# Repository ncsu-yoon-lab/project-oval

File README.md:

# Project OVAL

**Project On-campus Vehicle Autonomous Launch (OVAL)** is a research and development project aimed at designing an autonomous vehicle capable of navigating NC State University's campus. The project provides a platform for students to test autonomous vehicle algorithms in a real-world environment. Additionally, it opens possibilities for campus applications such as package delivery, security patrols, plant monitoring, or other autonomous tasks.

The system architecture includes:

* **Onboard Computer (Jetson Orin)** – Runs the ROS2 packages in this repo for perception, control, telemetry, and navigation.
* **GUI Computer** – Provides a graphical interface for monitoring and control.
* **AWS EC2 Web Server** – Optional remote server for logging, telemetry, or additional processing.

💡 *Suggested addition:* A system diagram showing the connections between Jetson, sensors, GUI, and AWS could help new users visualize the setup.

---

## Repository Layout

This repo is a ROS2 `colcon` workspace `src/` checkout: every top-level `project_oval_*` folder is an independent `ament_python` package, discovered automatically when you run `colcon build` from the workspace root. There is no single monolithic package anymore — functionality is split by subsystem so each package can be built, tested, and depended on independently.

```
project_oval/                       # this repo (colcon workspace src/ checkout)
├── project_oval_control/           # driving & actuation
├── project_oval_perception/        # camera / ML perception
├── project_oval_telemetry/         # sensors & comms
├── project_oval_navigation/        # graph-based global navigation
├── project_oval_bringup/           # launch files, URDF, Webots world
├── PyVESC/                         # vendored VESC motor-controller protocol library
├── archive/                        # retired subsystems, excluded from the build (COLCON_IGNORE)
├── tools/                          # standalone scripts that aren't ROS packages
├── README.md
├── requirements.txt                # pip dependencies for all packages below (see Building)
├── ros2_command_guide.md           # colcon/ros2 command cheat sheet
└── version_control_guide.md        # day-to-day git command cheat sheet
```

Build everything with:

```bash
python3 -m pip install -r src/project_oval/requirements.txt   # once per machine — colcon doesn't do this for you
cd ~/ros2_ws   # workspace root, one level above src/
colcon build
source install/setup.bash
```

Build a single package while iterating:

```bash
colcon build --packages-select project_oval_control --symlink-install
```

`ros2 run`/`ros2 launch` won't find these packages until you `source install/setup.bash` in your current shell (a fresh terminal needs this every time, or add it to `.bashrc`) — see [`ros2_command_guide.md`](ros2_command_guide.md) for that and other frequently-used `colcon`/`ros2` commands.

### `project_oval_control` — driving & actuation

Turns steering/throttle/lane-following decisions into motor commands, and reads the Xbox controller for manual/teleop driving. Depends on the vendored `PyVESC/` library to talk to the VESC motor controllers over serial, plus `gps_msgs`/`nmea_msgs` for GPS-based pursuit.

| Run with | Purpose |
|---|---|
| `ros2 run project_oval_control driver` | Sends throttle/steering commands to the VESC motor controllers. |
| `ros2 run project_oval_control lane_follower` | PID lane-centering control from a segmented edge-distance signal. |
| `ros2 run project_oval_control xbox_controller` | Reads Xbox controller input (via `joy_node`) and republishes it as drive commands. |
| `ros2 launch project_oval_control manual_control.launch.py` | Brings up `joy_node` + `xbox_controller` + `driver` together for manual/teleop driving. |

Also included (not standalone nodes): `sim_driver_lib.py`/`sim_driver_node.py` (the `SimDriverNode` Webots plugin, wired up via `project_oval_bringup/urdf/my_robot.urdf` for simulation), `PIDController.py` (shared PID implementation), and `pursuitNode.py`/`test_lib.py` (older GPS-pursuit and manual test scripts, kept for reference — not registered as console scripts).

### `project_oval_perception` — camera & ML perception

Runs the computer-vision and ML models on camera input: sidewalk/lane segmentation and object detection.

| Run with | Purpose |
|---|---|
| `ros2 run project_oval_perception segmentation` | ONNX Runtime lane/sidewalk segmentation on the ZED camera feed. |
| `ros2 run project_oval_perception sidewalk_segmentation` | Transformer-based (Segformer) sidewalk segmentation using the bundled `sidewalk_segmentation_model/` weights. |
| `ros2 run project_oval_perception obstacle_detector` | LaserScan-based obstacle detection; publishes a brake/stop signal. |
| `ros2 run project_oval_perception yolo_od` | YOLO object detection on the camera feed. |
| `ros2 run project_oval_perception zed` | Publishes raw ZED camera images as a ROS2 topic. |

`lane_detector.py`/`simple_lane_detection.py` are shared detection library code (also imported by `project_oval_control`'s `lane_follower_node`). `docs/onnx_runtime_install_guide.md` has the ONNX Runtime GPU install steps for Jetson/ARM64.

> ⚠️ `segmentation_node.py`'s default model path and `test.py` still point at a contributor's personal machine (`/home/wolfwagen1/...`) and reference an ONNX model (`dino_segmentation_2.onnx`) that isn't checked into this repo. Point `model_path` at a real model (e.g. the bundled `sidewalk_segmentation_model/`) before relying on the `segmentation` executable.

### `project_oval_telemetry` — sensors & communications

Reads and republishes sensor/GPS data, bridges to external systems (a serial radio link, Google Cloud Pub/Sub), and displays status.

| Run with | Purpose |
|---|---|
| `ros2 run project_oval_telemetry imu` | Logs ZED IMU data to CSV. |
| `ros2 run project_oval_telemetry fake_rtk` | Publishes a synthetic RTK/GPS fix for testing without hardware. |
| `ros2 run project_oval_telemetry zed_heading` | Computes vehicle heading from magnetometer/IMU data. |
| `ros2 run project_oval_telemetry telemetry_ros2` | Serial bridge node — relays ROS2 messages to/from a radio-connected Raspberry Pi. |
| `ros2 run project_oval_telemetry pub_sub_google` | Publishes telemetry to a Google Cloud Pub/Sub topic. |
| `ros2 run project_oval_telemetry oval_message` | Publishes rotating status/sponsor messages to `/oval_message`. |
| `ros2 run project_oval_telemetry message_display` | Tkinter GUI that displays whatever `oval_message` is currently publishing. |
| `ros2 run project_oval_telemetry map_test` | Manual test script: parses NMEA GPS fixes and renders them on a Folium map. |

`export_imu_csv.py`/`export_rosbag_video.py` are offline analysis scripts for pulling IMU CSVs and depth video out of a recorded rosbag — run directly with `python3`, not as ROS nodes.

### `project_oval_navigation` — graph-based global navigation

A self-contained global-navigation stack: waypoint-graph planning over campus, EKF/RTK localization, pure-pursuit path following, and a browser dashboard for launching/monitoring the other nodes. See `project_oval_navigation/README.md` for the full waypoint/graph format and startup sequence.

| Run with | Purpose |
|---|---|
| `ros2 run project_oval_navigation global_planner_node` | Plans a route through the waypoint graph (`maps/graph_nodes.csv`, `maps/graph_edges.csv`). |
| `ros2 run project_oval_navigation global_set_reference` | Captures a lat/lon reference origin from the current RTK GPS + ZED pose. |
| `ros2 run project_oval_navigation pure_pursuit_node` | Pure-pursuit path following against the planned route. |
| `ros2 run project_oval_navigation oval_web_ui` | Local web dashboard for starting/stopping the nodes above (and the manual driver/Xbox controller from `project_oval_control`). |
| `ros2 launch project_oval_navigation sensors_bringup.launch.py` | Brings up the sensor stack needed for localization. |
| `ros2 launch project_oval_navigation localization.launch.py` | Runs the `robot_localization` EKF/navsat filters. |
| `ros2 launch project_oval_navigation control_nodes.launch.py` | Launches driver + xbox_controller (from `project_oval_control`) + pure pursuit together. |
| `ros2 launch project_oval_navigation rtk_control.launch.py` | Full localization + control stack for RTK-based driving. |

This package depends on `project_oval_control` at run time (for the `driver` and `xbox_controller` executables used by its launch files and web UI).

### `project_oval_bringup` — launch, URDF, simulation world

No nodes of its own — orchestrates the others.

* `launch/car_sim_launch.py` — launches the Webots simulator with `worlds/test_world.wbt` and attaches `project_oval_control`'s `SimDriverNode` via `urdf/my_robot.urdf`.
* `urdf/my_robot.urdf` — robot description used by the Webots driver plugin.
* `worlds/test_world.wbt` — the Webots simulation world.

```bash
ros2 launch project_oval_bringup car_sim_launch.py
```

### Other top-level folders

* **`PyVESC/`** — vendored copy of [LiamBindle/PyVESC](https://github.com/LiamBindle/PyVESC) (VESC motor controller serial protocol). Not a ROS package; `project_oval_control` imports it as a regular Python dependency.
* **`archive/`** — retired code kept for reference, marked with `archive/COLCON_IGNORE` so colcon skips it during a build. Currently holds `project-oval_legacy_sidewalk/`, the earlier LIDAR + sidewalk-following subsystem.
* **`tools/`** — scripts that aren't ROS packages and aren't built by colcon, e.g. `tools/gemini_chatbot/` (voice/chat control demo scripts, run directly with `python3`).

---

## Startup Sequence for Onboard Computer (Jetson Orin)

The Jetson Orin runs several ROS2 nodes to interface with the vehicle hardware. The primary ones are:

| Node | Package | Purpose |
|---|---|---|
| `joy_node` | `joy` (external) | Reads XBox controller inputs |
| `swiftnav_ros2_driver` | `swiftnav_ros2_driver` (external) | Interfaces with the Piksi Multi GNSS |
| `zed_camera` | `zed_wrapper` (external) | Streams stereo camera data |
| `xbox_controller` | `project_oval_control` | Turns joystick input into drive commands |
| `driver` | `project_oval_control` | Sends commands to the motors |

---

### **Joy Node**

Outputs joystick inputs from the XBox controller.

```bash
ros2 run joy joy_node --ros-args -p autorepeat_rate:=20.0
```

---

### **Manual Driving (Joy + Xbox Controller + Driver)**

Brings up `joy_node`, `xbox_controller`, and `driver` together in one command — the quickest way to get manual/teleop driving running.

```bash
ros2 launch project_oval_control manual_control.launch.py
```

---

### **Lidar Node**

Outputs Lidar Pointcloud.

```bash
ros2 launch velodyne velodyne-all-nodes-VLP16-launch.py
```

To viz:

```bash
rviz2 ## change to velodyne frame
```

---

### **Message Display**

Show the Team and other messages.

```bash
ros2 run project_oval_telemetry message_display   # shows the GUI
ros2 run project_oval_telemetry oval_message       # publishes messages for the GUI to display
```

---

### **Gemini Voice Controller**

Control the robot using voice commands. This is a standalone script (`tools/`), not a ROS package.

```bash
python3 tools/gemini_chatbot/wolfwagen_live_demo.py ## To show GUI and listen
```

---

### **Radio Raspberry Pi Control**

Bridges ROS2 messages to a radio-connected Raspberry Pi over serial.

```bash
ros2 run project_oval_telemetry telemetry_ros2 ## To connect to Radio
```

---

### **ZED Camera Node**

Outputs ZED camera topics. Documentation: [Stereolabs ZED ROS2 Node](https://www.stereolabs.com/docs/ros/zed-node).

```bash
ros2 launch zed_wrapper zed_camera.launch.py camera_model:=zed2i
```

#### ZED2i Setup

1. **Check CUDA installation**

```bash
nvidia-smi
```

2. **Install ZED SDK**
   Follow the [official ZED SDK installation instructions](https://www.stereolabs.com/developers/release/latest/) for NVIDIA Jetson. This may take \~30 minutes.

3. **Set up the environment**
   Follow the [ROS2 environment setup instructions](https://www.stereolabs.com/docs/ros2).

💡 *Suggested addition:* Include instructions for testing the ZED camera stream after setup.

---

### **RTK Piksi Multi Setup**

Setup instructions for the SwiftNav Piksi Multi ROS2 package.

#### Step 1 – Installation

Follow the [SwiftNav ROS2 package instructions](https://github.com/swift-nav/swiftnav-ros2).

#### Step 2 – TCP Connection Setup

If TCP connection issues occur, set up the Jetson Ethernet interface manually:

```bash
sudo ip addr add 192.168.0.100/24 dev eno1
ping 192.168.0.222
```

#### Step 3 – Optional USB Setup

USB may be preferable to avoid Ethernet setup. Some RS232-to-USB adapters may not work on the Jetson due to missing drivers.

Check for the PL2303 driver:

```bash
zcat /proc/config.gz | grep -i 'pl2303'
```

If it returns `#CONFIG_USB_SERIAL_PL2303 is not set`, use an FTDI or CH340/CH341 adapter.

#### Step 4 – Run the Node

```bash
ros2 launch swiftnav_ros2_driver start.py
```

💡 *Suggested addition:* Add a small troubleshooting section for common GNSS issues (e.g., no fix, bad TCP connection).

---

### **PyVESC Library Setup**

PyVESC is already vendored in this repo at `PyVESC/` (unmodified copy of [LiamBindle/PyVESC](https://github.com/LiamBindle/PyVESC) v1.0.5) — you don't need to clone it separately.

#### Step 1 – Install it in editable mode

```bash
cd ~/ros2_ws/src/project_oval
python3 -m pip install -e PyVESC/
python3 -m pip install pyserial
```

#### Step 2 – Build and test the driver node

```bash
cd ~/ros2_ws
colcon build --packages-select project_oval_control --symlink-install
source install/setup.bash
ros2 run project_oval_control driver
```

💡 *Suggested addition:* Include instructions for ROS2 integration with PyVESC and how to verify motor actuation.

---

# GitHub Contribution Guidelines

This repository follows a lightweight but strict Git workflow to keep development organized, reviewable, and stable—especially important for autonomous vehicle development where software, simulation, and hardware intersect.

Please read and follow these rules before contributing. For everyday git commands (branching, pulling, pushing), see [`version_control_guide.md`](version_control_guide.md).

---

## 1. Branch Lifespan

**Branches should be short-lived.**

- If you create a new branch, it should be **merged or closed within 7 days**.
- If work is ongoing past a week:
  - Open a pull request with incremental progress, or
  - Clearly note why the branch is staying open.

This helps prevent abandoned branches and keeps development moving.

---

## 2. Pull Requests for All Changes

**All changes must go through pull requests.**

- Any successful or functional change—no matter how small—should be submitted as a pull request.
- Draft pull requests are encouraged for incomplete or in-progress work.
- This applies even if you are the only one working on the branch.

Pull requests are used to track changes to `main`, discuss design decisions, and preserve project history.

---

## 3. One Purpose per Branch

**Each branch should have a single, clear purpose.**

- Avoid mixing unrelated changes in the same branch.
- Examples of unrelated changes:
  - Sensor drivers + visualization tweaks
  - Control logic + documentation cleanup

Keeping branches focused makes reviews, testing, and debugging significantly easier.

---

## 5. Pull Request Descriptions

**Every pull request must include:**

- **What changed**
- **Why it changed**
- **How it was tested**
  - Simulation
  - Hardware
  - Log playback
  - Or explicitly state if it was not tested

Clear PR descriptions save time and reduce misunderstandings.

---

## 6. No Direct Pushes to `main`

**Direct pushes to `main` are not allowed.**

- All changes must be merged through pull requests.
- This rule applies to everyone, regardless of role.

This ensures visibility, review, and traceability of all changes.

---

## 7. Keep `main` Runnable

**The `main` branch must always build and run.**

- Do not merge changes that break:
  - Builds
  - Simulation
  - Deployment pipelines
- If a change introduces a breaking issue, it must be fixed before merging.

`main` should always represent a stable, usable state of the project.

---

## 8. Commit Hygiene

**Commits should be clear and intentional.**

- Use descriptive commit messages.
- Avoid vague messages like:
  - `wip`
  - `fix`
  - `stuff`
- Each commit should represent a coherent, logical change.

Good commit history makes debugging, reverting, and collaboration far easier.

---

## Final Notes

These rules exist to:
- Prevent branch sprawl
- Keep `main` stable
- Make collaboration and review painless
- Save time during testing, deployment, and field work

If something doesn't fit neatly into these rules, communicate early via a pull request or discussion.

### **Additional Recommendations for README**

1. **System Requirements:** List Jetson OS version, ROS2 version, Python version, and minimum hardware requirements.
2. **Startup Script:** Consider creating a single script to launch all nodes in the correct order.
3. **Troubleshooting Section:** Include common error messages for ROS2, ZED, Piksi Multi, and PyVESC.
4. **Data Logging:** Provide instructions for recording sensor or GNSS data for research purposes.
5. **References:** Include links to relevant ROS2, ZED, Piksi, and PyVESC documentation for quick reference.

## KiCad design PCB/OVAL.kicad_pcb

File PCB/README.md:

# Project OVAL PCB

## Overview
The electronics system is designed and developed with the use of [KiCAD](https://www.kicad.org/) to incorporate the entire electrical system into a printed circuit board (PCB). The PCB will be manufactured by [JLCPCB](https://jlcpcb.com/). Developing a custom PCB will provide consistent connections and further adjustments as new revisions are made on the PCB.

## KiCAD Version Control
You can access the project by importing the .proj file in this directory. Do not change anything unless collaborating with other members.

## Next Steps
* Schematic needs to be checked
* Test ATTiny85 with I2C and PPM generation
* Figure out wiring for back LEDs
* Power switch for ESC
* Make the ESC directly attach to the PCB
* Remove the electromagnets
* Include a voltage sensor

## Components
Below are the descriptions of all the components considered and incorporated into the PCB

### Power
The power for the whole system is sourced from two [4s LiPo batteries](https://www.amazon.com/dp/B07Y1PYHKC?ref_=ppx_hzsearch_conn_dt_b_fed_asin_title_2). Turning the power on and off is directly controlled by a [DPDT switch](https://www.amazon.com/Twidec-Rocker-Toggle-Position-Waterproof/dp/B07LBMMN2Y/ref=sr_1_3?dib=eyJ2IjoiMSJ9.H1GVn0sV9nroy_uFaZHPdd5zl96OmoEBumcDbs2H2JQsCQWccp83BUf9UMrdTw5yn2Gh-R7XMM7Rhy0J8cPQUunQYQQI-I8DpZY4GHWhhZfa_H08-9tdhQhasKEfKwsORwEHOc4Qq9w2f_awsDMn9SciTHHxJvrF6eQ4TpXpnHJhAdd_uB5lI0awRb96oNr2xs-qYPh7MeJv7FwMkOd6xVZB6cMgUIFhQ-2nyexbUGw.bw0kXIxRu6rnZ9yNmepIGsJ9vjd-tjA7nIPwPtc036g&dib_tag=se&keywords=double%2Bpole%2Bdouble%2Bthrow%2Bswitch&qid=1748457096&sr=8-3&th=1). The power then goes through a [buck converter](https://www.amazon.com/WWZMDiB-Converter-Adjustable-Regulator-Protection/dp/B0B825HRB9/ref=sr_1_3?crid=X0NHTXOBZQBN&dib=eyJ2IjoiMSJ9.OVZkkMvTynFktJV0_FpqOz9G-79GCf5LbvPXwQiyANJTXUIdp-s9YyWXiubRIaMcQTqaOvUStJel0N4QgSzktCbwemDFsNzsKFPukLzzg9BAYQ7lPAzqoRV9t5gccvsWanqf6VVNeu8hhikXhyIUT0Np_qtc4yjpI7uwknCNYr7hk-_KrTu2k3UAdGd2GWSzxy316hXX1D9F4PrttX0l6_WxYWf5SUisVcA2T02Gyiw._XYZ6-QOanhcWZ5D29KLau23OnrpKjCr3EAjNbOWu8I&dib_tag=se&keywords=buck+converter+high+current&qid=1748453761&sprefix=buck+converter+high+current%2Caps%2C113&sr=8-3) to convert the output of the batteries to 12VDC and a max of 20A. This power will go to several features: cooling system, NVIDIA Jetson Orin AGX, monitoring LED, and the external 12VDC plug on the panel. A DC to DC converter is used to then convert the 12VDC to 5VDC to power the front LED and the touch screen.

### Charging
The batteries are expected to remain inside the electronics box at all times and are only able to be charged and discharged when the system is turned off via the [DPDT switch](https://www.amazon.com/Twidec-Rocker-Toggle-Position-Waterproof/dp/B07LBMMN2Y/ref=sr_1_3?dib=eyJ2IjoiMSJ9.H1GVn0sV9nroy_uFaZHPdd5zl96OmoEBumcDbs2H2JQsCQWccp83BUf9UMrdTw5yn2Gh-R7XMM7Rhy0J8cPQUunQYQQI-I8DpZY4GHWhhZfa_H08-9tdhQhasKEfKwsORwEHOc4Qq9w2f_awsDMn9SciTHHxJvrF6eQ4TpXpnHJhAdd_uB5lI0awRb96oNr2xs-qYPh7MeJv7FwMkOd6xVZB6cMgUIFhQ-2nyexbUGw.bw0kXIxRu6rnZ9yNmepIGsJ9vjd-tjA7nIPwPtc036g&dib_tag=se&keywords=double%2Bpole%2Bdouble%2Bthrow%2Bswitch&qid=1748457096&sr=8-3&th=1). The batteries will be ran in parallel to extend the battery life of the 2 4s LiPo batteries to last an hour of driving at half speed.

### Motor Control
Each motor will be driven via an [ATTiny85](https://www.microchip.com/en-us/product/attiny85). The two ATTiny85s are an AVR that will be on an I2C bus with the NVIDIA Jetson Orin AGX as the parent to receive a command on the throttle. The ATTiny85 will separately output a PPM signal to the ESCs to control the throttle of the motors. Currently untested.

### Access Panel
Inside the tailgate of the system there will be an access panel to all the features inside the electronics box to avoid having to remove the electronics box at any time. The access panel will include charging ports for battery 1 and 2, USB A and USB C ports to the Orin, pins to the Orin, OLED screen displaying battery life, LED displaying power on/off, display port to the Orin, and the toggle switch for powering the system, and a DC jack to access 12VDC if needed for testing.

## [Current parts list](https://docs.google.com/spreadsheets/d/1QfchhVsQ0_ZyLnvvQ3l3CDZhC2zzI9vGqhxGo_DR1Cs/edit?usp=sharing)
Feel free to add new parts if needed.

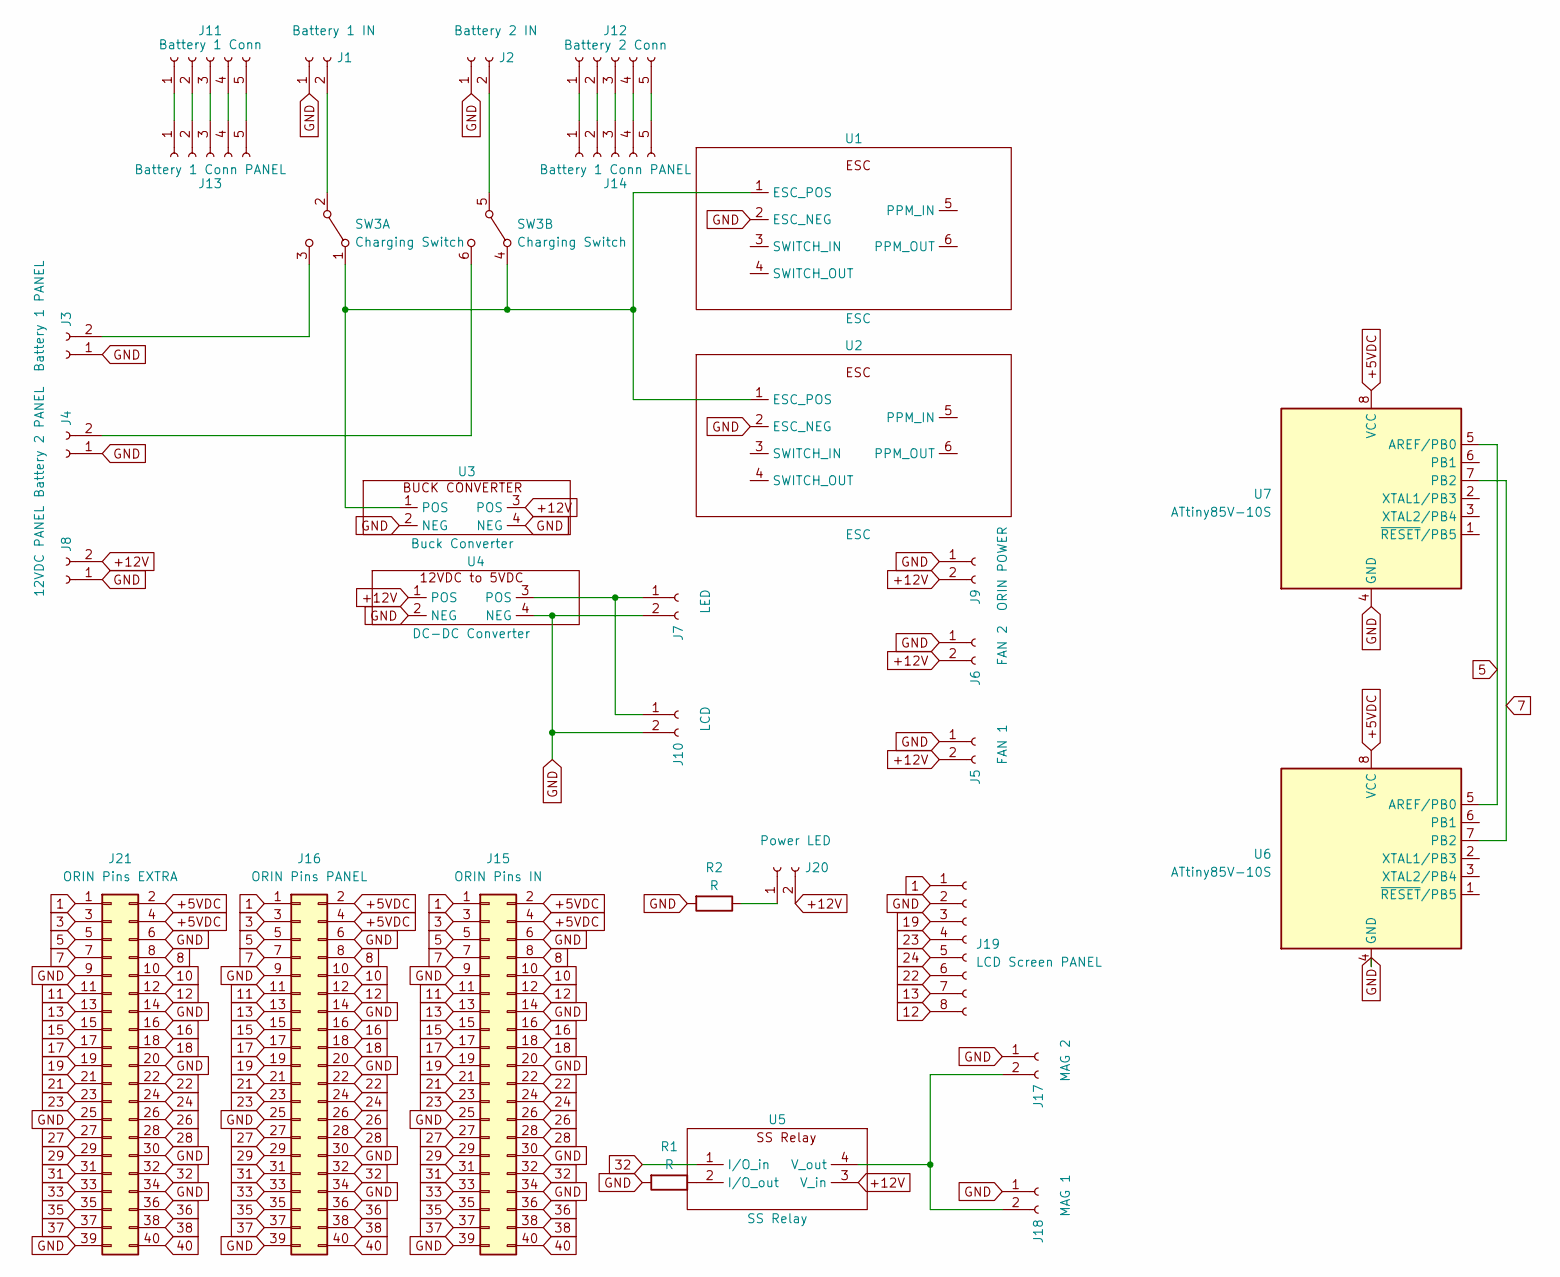
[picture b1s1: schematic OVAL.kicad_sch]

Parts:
J1: Battery 1 IN; BATTERY
J2: Battery 2 IN; BATTERY
J3: Battery 1 PANEL; BATTERY
J4: Battery 2 PANEL; BATTERY
J5: FAN 1; PinSocket_1x02_P2.54mm_Vertical
J6: FAN 2; PinSocket_1x02_P2.54mm_Vertical
J7: LED; PinSocket_1x02_P2.54mm_Vertical
J8: 12VDC PANEL; BATTERY
J9: ORIN POWER; PinSocket_1x02_P2.54mm_Vertical
J10: LCD; PinSocket_1x02_P2.54mm_Vertical
J11: Battery 1 Conn; PinSocket_1x05_P2.54mm_Vertical
J12: Battery 2 Conn; PinSocket_1x05_P2.54mm_Vertical
J13, J14: Battery 1 Conn PANEL; PinSocket_1x05_P2.54mm_Vertical
J15: ORIN Pins IN; PinSocket_2x20_P2.54mm_Vertical
J16: ORIN Pins PANEL; PinSocket_2x20_P2.54mm_Vertical
J17: MAG 2; PinSocket_1x02_P2.54mm_Vertical
J18: MAG 1; PinSocket_1x02_P2.54mm_Vertical
J19: LCD Screen PANEL; PinSocket_1x08_P2.54mm_Vertical
J20: Power LED; PinSocket_1x02_P2.54mm_Vertical
J21: ORIN Pins EXTRA; PinSocket_2x20_P2.54mm_Vertical
R1, R2: R; R_Axial_DIN0207_L6.3mm_D2.5mm_P10.16mm_Horizontal
SW3: Charging Switch; PinSocket_1x06_P2.54mm_Vertical
U1, U2: ESC
U3: Buck Converter; Buck_Converter
U4: DC-DC Converter; DC-DC_Converter
U5: SS Relay; SS_Relay
U6, U7: ATtiny85V-10S; SOIC-8W_5.3x5.3mm_P1.27mm

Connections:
1: J15.1, J16.1, J19.1, J21.1
3: J15.3, J16.3, J21.3
5: J15.5, J16.5, J21.5, U6.5 (AREF/PB0), U7.5 (AREF/PB0)
7: J15.7, J16.7, J21.7, U6.7 (PB2), U7.7 (PB2)
8: J15.8, J16.8, J21.8
10: J15.10, J16.10, J21.10
11: J15.11, J16.11, J21.11
12: J15.12, J16.12, J19.8, J21.12
13: J15.13, J16.13, J19.7, J21.13
15: J15.15, J16.15, J21.15
16: J15.16, J16.16, J21.16
17: J15.17, J16.17, J21.17
18: J15.18, J16.18, J21.18
19: J15.19, J16.19, J19.3, J21.19
21: J15.21, J16.21, J21.21
22: J15.22, J16.22, J19.6, J21.22
23: J15.23, J16.23, J19.4, J21.23
24: J15.24, J16.24, J19.5, J21.24
26: J15.26, J16.26, J21.26
27: J15.27, J16.27, J21.27
28: J15.28, J16.28, J21.28
29: J15.29, J16.29, J21.29
31: J15.31, J16.31, J21.31
32: J15.32, J16.32, J21.32, U5.1 (I/O_in)
33: J15.33, J16.33, J21.33
35: J15.35, J16.35, J21.35
36: J15.36, J16.36, J21.36
37: J15.37, J16.37, J21.37
38: J15.38, J16.38, J21.38
40: J15.40, J16.40, J21.40
+5VDC: J15.2, J15.4, J16.2, J16.4, J21.2, J21.4, U6.8 (VCC), U7.8 (VCC)
+12V: J5.2, J6.2, J8.2, J9.2, J20.2, U3.3 (POS), U4.1 (POS), U5.3 (V_in)
GND: J1.1, J2.1, J3.1, J4.1, J5.1, J6.1, J7.2, J8.1, J9.1, J10.2, J15.6, J15.9, J15.14, J15.20, J15.25, J15.30, J15.34, J15.39, J16.6, J16.9, J16.14, J16.20, J16.25, J16.30, J16.34, J16.39, J17.1, J18.1, J19.2, J21.6, J21.9, J21.14, J21.20, J21.25, J21.30, J21.34, J21.39, R1.2, R2.2, U1.2 (ESC_NEG), U2.2 (ESC_NEG), U3.2 (NEG), U3.4 (NEG), U4.2 (NEG), U4.4 (NEG), U6.4 (GND), U7.4 (GND)
unnamed: J1.2, SW3.2 (B)
unnamed: J2.2, SW3.5 (B)
unnamed: J3.2, SW3.3 (C)
unnamed: J4.2, SW3.6 (C)
unnamed: J7.1, J10.1, U4.3 (POS)
unnamed: J11.1, J13.1
unnamed: J11.2, J13.2
unnamed: J11.3, J13.3
unnamed: J11.4, J13.4
unnamed: J11.5, J13.5
unnamed: J12.1, J14.1
unnamed: J12.2, J14.2
unnamed: J12.3, J14.3
unnamed: J12.4, J14.4
unnamed: J12.5, J14.5
unnamed: J17.2, J18.2, U5.4 (V_out)
unnamed: J20.1, R2.1
unnamed: SW3.1 (A), SW3.4 (A), U1.1 (ESC_POS), U2.1 (ESC_POS), U3.1 (POS)
unnamed: R1.1, U5.2 (I/O_out)

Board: 2 copper layers, 31 parts (0 on the bottom side), 52 nets, no tracks yet.

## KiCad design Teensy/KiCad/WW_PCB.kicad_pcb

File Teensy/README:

Teensy loader commands for ORIN:

sudo cp 00-teensy.rules /etc/udev/rules.d/
tar -xvzf teensy_linux64.tar.gz

To use the teensy loader:
./teensy &

Other resources:
https://www.pjrc.com/teensy/td_download.html

https://www.pjrc.com/teensy/loader_linux.html

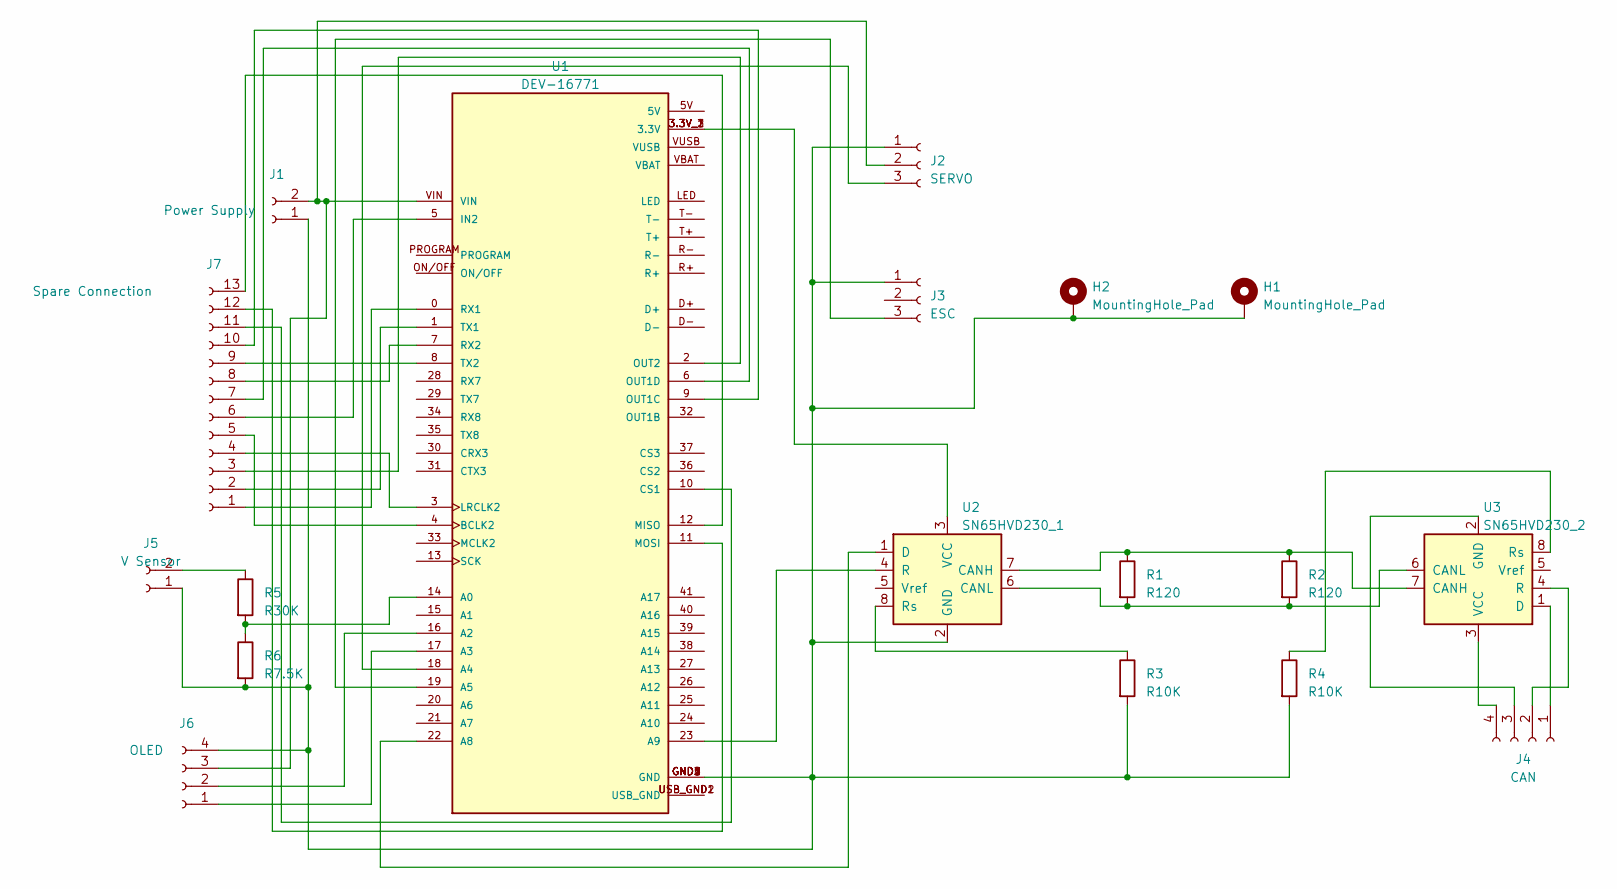
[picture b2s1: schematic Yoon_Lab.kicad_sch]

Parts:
H1, H2: MountingHole_Pad; MountingHole_3.2mm_M3_ISO14580_Pad
J1: Power Supply; PinSocket_1x02_P2.54mm_Horizontal
J2: SERVO; PinSocket_1x03_P2.54mm_Horizontal
J3: ESC; PinSocket_1x03_P2.54mm_Horizontal
J4: CAN; PinSocket_1x04_P2.54mm_Horizontal
J5: V Sensor; PinSocket_1x02_P2.54mm_Vertical
J6: OLED; PinSocket_1x04_P2.54mm_Vertical
J7: Spare Connection; PinSocket_1x13_P2.54mm_Vertical
R1, R2: R120; R_Axial_DIN0309_L9.0mm_D3.2mm_P12.70mm_Horizontal
R3, R4: R10K; R_Axial_DIN0309_L9.0mm_D3.2mm_P12.70mm_Horizontal
R5: R30K; R_Axial_DIN0309_L9.0mm_D3.2mm_P12.70mm_Horizontal
R6: R7.5K; R_Axial_DIN0309_L9.0mm_D3.2mm_P12.70mm_Horizontal
U1: DEV-16771; MODULE_DEV-16771; PARTREV 4.1
U2: SN65HVD230_1; SOIC-8_3.9x4.9mm_P1.27mm
U3: SN65HVD230_2; SOIC-8_3.9x4.9mm_P1.27mm

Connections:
unnamed: H1.1, H2.1, J1.1, J2.1, J3.1, J5.1, J6.4, R3.2, R4.2, R6.2, U1.GND1 (GND), U1.GND2 (GND), U1.GND3 (GND), U1.GND4 (GND), U1.GND5 (GND), U2.2 (GND)
unnamed: J1.2, J2.2, J6.3, U1.VIN
unnamed: J2.3, U1.18 (A4)
unnamed: J3.3, U1.19 (A5)
unnamed: J4.1, U3.1 (D)
unnamed: J4.2, U3.4 (R)
unnamed: J4.3, U3.2 (GND)
unnamed: J4.4, U3.3 (VCC)
unnamed: J5.2, R5.1
unnamed: J6.1, U1.17 (A3)
unnamed: J6.2, U1.16 (A2)
unnamed: J7.1, U1.0 (RX1)
unnamed: J7.2, U1.1 (TX1)
unnamed: J7.3, U1.2 (OUT2)
unnamed: J7.4, U1.3 (LRCLK2)
unnamed: J7.5, U1.4 (BCLK2)
unnamed: J7.6, U1.5 (IN2)
unnamed: J7.7, U1.6 (OUT1D)
unnamed: J7.8, U1.7 (RX2)
unnamed: J7.9, U1.8 (TX2)
unnamed: J7.10, U1.9 (OUT1C)
unnamed: J7.11, U1.10 (CS1)
unnamed: J7.12, U1.11 (MOSI)
unnamed: J7.13, U1.12 (MISO)
unnamed: R5.2, R6.1, U1.14 (A0)
unnamed: U1.22 (A8), U2.1 (D)
unnamed: U1.23 (A9), U2.4 (R)
unnamed: U1.USB_GND1 (USB_GND), U1.USB_GND2 (USB_GND)
unnamed: R1.1, R2.1, U2.7 (CANH), U3.7 (CANH)
unnamed: R1.2, R2.2, U2.6 (CANL), U3.6 (CANL)
unnamed: R3.1, U2.8 (Rs)
unnamed: U1.3.3V_1 (3.3V), U1.3.3V_2 (3.3V), U1.3.3V_3 (3.3V), U2.3 (VCC)
unnamed: R4.1, U3.8 (Rs)

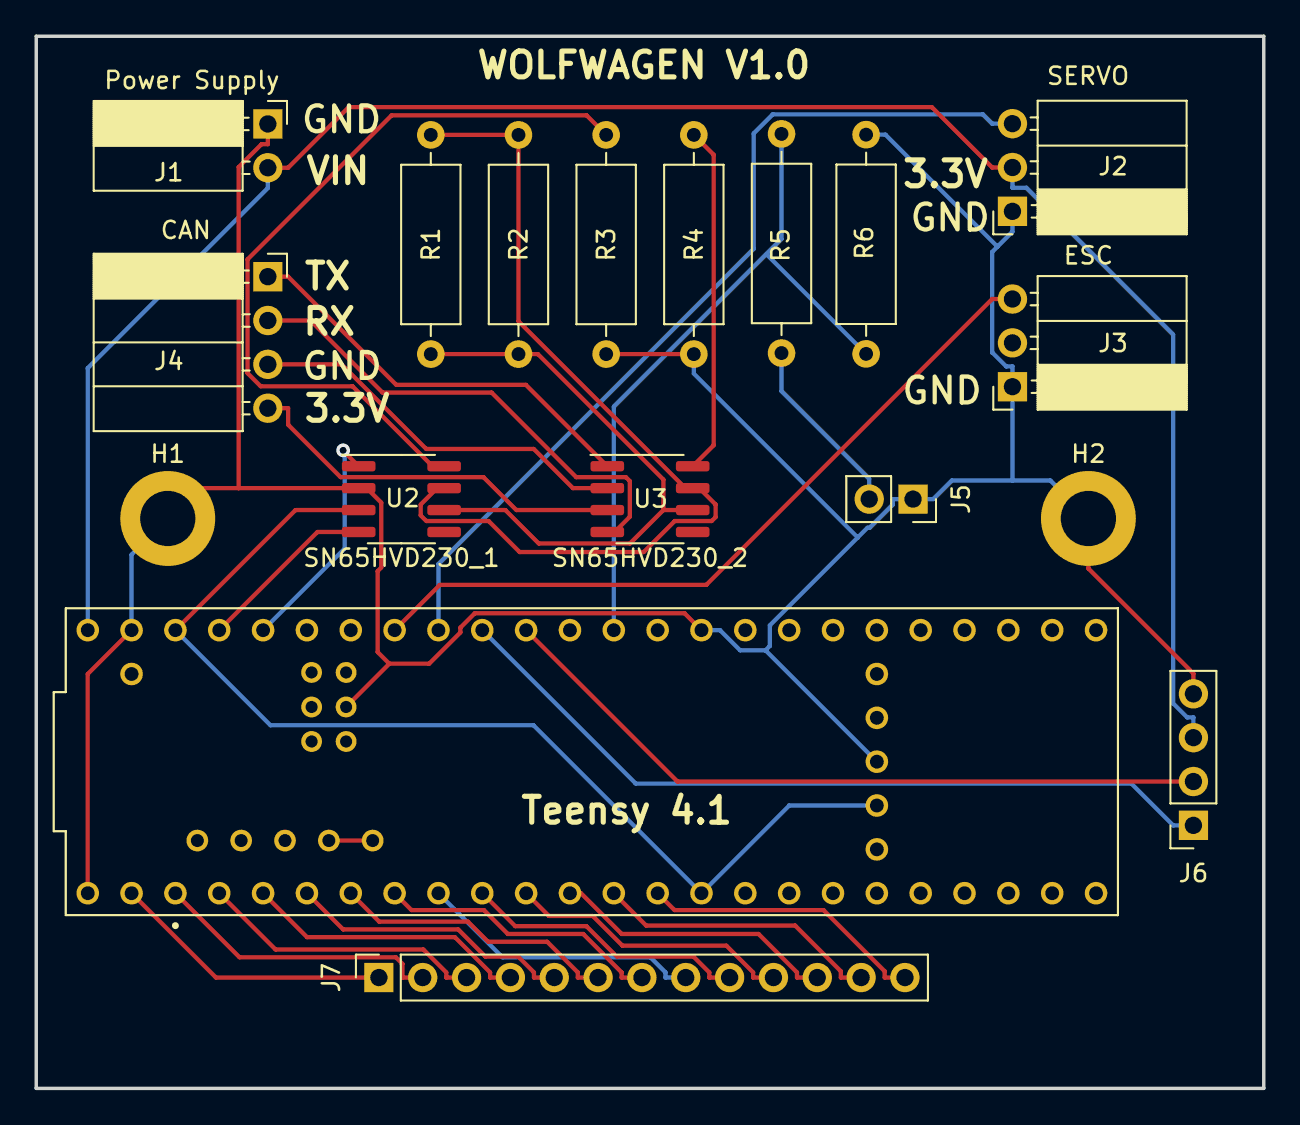
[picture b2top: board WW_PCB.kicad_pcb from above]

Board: 2 copper layers, 71.1 x 61.0 mm, 18 parts (0 on the bottom side), 33 nets.

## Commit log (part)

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2024-06-10 Rename node_gps.py to project-oval/node_gps.py
2024-06-10 Rename GUI/WW_Logo.png to GUI/Images/WW_Logo.png
2024-06-10 Rename GUI/blue_marker.png to GUI/Images/blue_marker.png
2024-06-10 Rename GUI/red_marker.png to GUI/Images/red_marker.png
2024-06-10 Rename WolfwagenBW.png to Wolfwagen-Horizontal-BW.png
2024-06-10 Rename Images/output-onlinepngtools.png to Wolfwagen-Horizontal-Red.png
2024-06-10 Rename Wolfwagen-Horizontal-Red.png to Images/Wolfwagen-Horizontal-Red.png
2024-06-10 Rename output-onlinepngtools (1).png to Wolfwagen-Round-Red.png
2024-06-10 Rename Wolfwagen-Horizontal-BW.png to WW-Horizontal-BW.png
2024-06-10 Rename Wolfwagen-Horizontal-Red.png to WW-Horizontal-Red.png
2024-06-10 Rename Screenshot 2024-06-10 191224.png to WW-Round-BW
2024-06-10 Rename WW_Logo.png to WW-Logo.png
2024-06-10 Rename WW-Round-BW to WW-Round-BW.png
2024-06-11 Rename node_pp_motor_act.py to node_motor_act.py
2024-06-13 Adding most current GUI
2024-06-13 Updating GUI
2024-06-13 Syncing github
2024-06-17 Working ONNX with ZED
2024-06-17 WIP: Integrated with existing code
2024-06-18 Updated GUI
2024-06-23 Updating
2024-06-24 Removed old GPS node
2024-06-24 Resolving merge conflicts
2024-06-24 Renamed GPS node
2024-06-24 New RTK node for reading Swift Nav GNSS system
2024-06-27 Updated GUI to have functioning research
2024-06-27 Updated server and GUI
2024-06-28 Rename __init__.py to __init__.py
2024-06-28 Rename coords_to_cartesian.py to coords_to_cartesian.py
2024-06-28 Rename node_imu.py to node_imu.py
2024-06-28 Rename node_process_image.py to node_process_image.py
2024-06-28 Rename node_pure_pursuit.py to node_pure_pursuit.py
2024-06-28 Rename node_rtk.py to node_rtk.py
2024-06-28 Rename node_ui.py to node_ui.py
2024-06-28 Rename node_vicon.py to node_vicon.py
2024-06-28 Rename node_xbox_controller.py to node_xbox_controller.py
2024-06-28 Rename zed2i.launch.py to zed2i.launch.py
2024-06-28 Test
2024-06-28 Removed test
2024-06-30 Updated GUI and simulator for GUI
2024-07-02 Additional modifications to nodes
2024-07-02 Adjusting coords to coords_to_cartesian
2024-07-03 First test
2024-07-03 Added a new node that captures images from zed
2024-07-03 ON field changes
2024-07-04 Updated with logger for testing pure pursuit
2024-07-04 REsults after test 2
2024-07-04 Updated GUI and csvs
2024-07-05 Fixed coords to cartesian
2024-07-05 Failed test with coords to cartesian
2024-07-05 Editing images captured_images
2024-07-05 Images including darker, darkest, and normal
2024-07-05 First official training session
2024-07-05 Editing location of image data
2024-07-05 Changed the name of data logger to match img label
2024-07-06 Updating merge issues
2024-07-06 Adding matlab code to show cheap gps vs good gps
2024-07-08 ML Test Commit
2024-07-08 Split the file into 2 parts, one for training and one for testing
2024-07-08 node_gps.py now uses ML model
2024-07-08 Added logger for zed pose
2024-07-10 Editing gps node
2024-07-10 Updated logger
2024-07-10 Updated gps node
2024-07-10 New logger
2024-07-10 Now logger includes error
2024-07-10 Organized image logger node
2024-07-10 Debugging image logger
2024-07-11 Test 5
2024-07-12 Inital push
2024-07-12 Updated Matlab Code
2024-07-12 Added image preprocessing notebook
2024-07-12 Conda Env Dependencies For Training
2024-07-12 Overview of Paper
2024-07-13 Changing image shape (320,240) with annotation
2024-07-14 Model Setup
2024-07-14 Fixing the warning @RCNN
2024-07-15 Adding an auto_labeler
2024-07-15 Included manual selection for demo
2024-07-16 RCNN model training code
2024-07-23 bringing them up to date
2024-07-23 Adding jyupter note
2024-07-23 Adding jupyter file
2024-07-23 Added bug fix to cocodataset.py to skip any missing image files
2024-07-23 Model training code
2024-07-23 Conda Environment
2024-07-24 Tried running the model
2024-08-01 Test building detection
2024-08-02 Label Training
2024-08-04 New Model Prediction
2024-08-06 Data prep
2024-08-08 Script for FFNN
2024-08-08 Trained new landmark detection model. Working on testing
2024-08-09 Testing the performance of model5
2024-08-12 Filtering dataset
2024-08-12 Combined model traning
2024-08-13 Minor changes with architecture
2024-08-14 new lstm
2024-08-16 Change the arct.
2024-08-16 Changed compass model architecture, improved error
2024-08-23 Include lat/lon prediction model
2024-08-23 added model arch
2024-08-23 Folder for just localization
2024-08-23 Setup for localization for orin
2024-08-25 Faster RCNN Model with openCV test
2024-08-25 Working code to test RCNN inferences
2024-08-26 Tried a different arch for compass model, no real improvement
2024-08-28 Changing the shape of image
2024-08-28 Script to Change img shape and ligher model
2024-08-28 Modified log
2024-08-29 Loading light weight model
2024-09-02 Adding YOLO Model arch
2024-09-06 Code to get the inference of both image and lat lon
2024-09-06 Tested FFNN for compass prediction
2024-09-06 Working on getting the prediction
2024-09-07 Finished rcnn+ffnn with 3
2024-09-08 Added arch
2024-09-08 Finished testing RCNNwithFFNN
2024-09-10 file that tests different models
2024-09-11 Adding CompassArchLSTM
2024-09-14 Inference Scatter Plot result
2024-09-14 Modified scatter plot format jpg, png, pdf
2024-09-14 Testing Inference with Image+LatLon+Compass
2024-09-15 Revised Inference Plot
2024-09-17 plotter
2024-12-21 Training code for sidewalk segmentation from Hugging-Face
2025-01-10 Cleaning out for project oval
2025-01-10 Removing q-loc from project oval
2025-01-10 Organized for ROS2 and segmentation
2025-01-14 Prepared driver node
2025-01-17 removed auto from arduino
2025-01-17 Works with 1 arduino
2025-01-17 Works with 1 arduino actually
2025-01-21 Started python script for testing model
2025-01-21 Working segmenation code
2025-01-22 Segmentation working, adjusting path following
2025-01-29 new code
2025-01-29 working through integrating canny
2025-01-29 Making mid lines
2025-01-29 finding center of line
2025-02-02 Driver and xbox controller tested and ready for steering
2025-02-02 Improving following right side of lane - not finished
2025-02-02 Ready for testing
2025-02-03 Sidewalk segmentation test in progress
2025-02-03 Sidewalk segmentation tester
2025-02-04 Driving working!!!
2025-02-06 Removed some files and started other set up
2025-02-06 Created a setup script
2025-02-11 Velodyne visualization
2025-02-11 changes before jack
2025-02-11 WE'RE SO BACK
2025-05-02 first sgil test
2025-05-29 Adding PCB
2025-05-29 Delete sidewalk-segmentation directory
    Mistakenly added
2025-05-29 README for PCB
2025-05-29 New PCB reamde
2025-05-29 Path segmentation and testing
2025-05-29 Real time segmentation with zed
2025-05-31 Updated segmentation test
2025-05-31 WIP: ONNX model conversion
2025-05-31 Finished onnx file format
2025-06-03 Manual control with UART to VESC
2025-06-03 Lane follower node prepared for testing
2025-06-03 Driving :)
2025-06-03 Set up Onnx segmentation
2025-06-04 Sidewalk segmentation working, ready for video testing
2025-06-04 Video developer, needs to be tested
2025-06-04 Working video
2025-06-04 Lane detector ready for implementation
2025-06-04 Current on-board
2025-06-09 WIP: Working on Telemetry
2025-06-09 Working RTK radio transmitter
2025-06-09 Merging to use on second orin
2025-06-09 pushing to new orin
2025-08-22 Including PyVESC and documentation
2025-08-28 New upload
2025-08-28 Current oval setup
2025-09-02 Initial commit from new on-board orin
2025-09-02 Removed pyvesc temporarily
2025-09-02 Added pyvesc without git roots
2025-09-04 New readme
2025-09-09 Fixed VESC for Jetpack 6.2
2025-09-16 Updated Node for segmentation model
2025-09-18 Making new branch to merge random main changes
2025-09-18 New updates to the lane detector class to work with the segmented image
2025-09-22 New lane detector
2025-09-22 updated segmentation, zed, and driver code
2025-09-22 updated image mask to include a convex hull to cover patches
2025-09-23 Adding path detector test
2025-09-28 Improved lane follower node]
2025-09-28 Including path planner
2025-09-28 Moved the test dir to the project-oval dir
2025-09-28 Added path planner libary
2025-09-29 pushing sample path - ryan
2025-10-06 WIP: Created a topic for seg_viz
2025-10-13 late night commit for riot
2025-10-15 Implement input and output transcription
    Added input and output transcriptions during conversation handling.
2025-10-16 Delete gemini_chatbot/.env
    You should never upload a .env file to a git repo!
2025-10-16 Update .gitignore
    Ignore all .env
2025-10-16 riot stuff & pure pursuit
2025-10-17 message update
2025-10-18 pursuit node updates
2025-10-18 late night push open house
2025-10-22 track data
2026-01-24 Adding webots resource files to oval package
2026-01-24 Adding webots dependencies
2026-01-24 Adding sim configuration and changing python module name to project_oval
2026-01-24 changing python module name to project_oval so it can be imported
2026-01-24 modifying lidar topic name to match
2026-01-24 adding project file
2026-01-24 creating send_speeds method
2026-01-24 Completing sim support for xbox control
2026-01-30 Adding launch instructions to top of sim file
2026-01-31 Drive sim lib
2026-01-31 modifying to support reverse
2026-01-31 modifying to support reverse in sim
2026-01-31 fixing steering issue
2026-01-31 Adding friction properties to sim
2026-01-31 increasing rolling friction
2026-02-02 adjusting friction and torque scaling to car can turn
2026-02-10 Adjusted readme
2026-02-24 starting pure pursuit work
2026-02-24 refactoring 1
2026-02-24 refactoring 2 - does not have to be permanent
2026-02-24 last refactoring
2026-02-24 setting up pure pursuit file structure
2026-02-24 pure pursuit skeleton
2026-02-24 modifying diff. drive model
2026-02-24 last commit
2026-02-24 Adding GPS and IMU to sim car for Pure Pursuit
2026-02-24 starting work on pure pursuit algorithm
2026-02-25 improving path point readability
2026-02-25 completed circle intersection code for pure pursuit
2026-02-25 silly mistakes lol
2026-02-25 rough pure pursuit algorithm impl
2026-02-25 fixing typos and adding an end condition
2026-02-25 Complete untested pure pursuit algorithm
2026-02-25 handing degenerate segments
2026-02-25 Working on pure pursuit node and PID controller
2026-02-26 Finishing pure pursuit node (untested in sim)
2026-02-26 adding pure pursuit to console scripts
2026-02-26 Initial testing on sim
2026-02-28 working on local llm pipeline tts and stt
2026-02-28 updated files
2026-03-01 more
2026-03-01 chnage piper model
2026-03-01 piper req
2026-03-01 adding code to support pure pursuit on physical car
2026-03-01 adding imports
2026-03-01 adding some simple instructions to test on sim
2026-03-01 more changes
2026-03-01 changing vad
2026-03-02 update the gemini model
2026-03-02 new gui
2026-03-02 added text
2026-03-02 changed logo
2026-03-02 final changes
2026-03-26 small fix
2026-03-27 Updating sim to work with PyVesc (part 1)
2026-03-27 Tuning pure pursuit parameters and adding overshoot prevention
2026-03-28 [Implementation] Current onboard with LLM and set_rpm
2026-03-28 Removed git features for pyvesc library
2026-03-28 update segments for lookahead edge cases
2026-03-29 sim updates
2026-03-30 Scaling up sim for pedestrian support
2026-03-30 pedestrians added for collision avoidance testing
2026-04-05 Adding gateway node for security.
2026-04-10 Some fixes after sim scaling
2026-04-10 Prepping for massive overhaul of existing control server
2026-04-10 refactoring, alot.
2026-04-10 Adding config file, and adding back in OG web stuff
2026-04-10 updates to lib
2026-04-10 we want to check on every endpoint
2026-04-10 removing frontend
2026-04-11 web server overhaul: it was a long night and early morning
2026-04-11 Updates to gateway node Path vs Path imports
2026-04-11 config updates
2026-04-11 No idea how httpx is building the ssl context, so do it manually
2026-04-11 removing debugging code
2026-04-11 Web app testing finished
2026-05-04 new changes
2026-05-04 added fallback
2026-05-04 some other check"
2026-05-05 saving changes
2026-05-05 Pre-outdoor field test
2026-05-05 rtk test
2026-05-05 Pushing from cole's laptop
2026-05-05 Working llm
2026-05-05 Working llm node
